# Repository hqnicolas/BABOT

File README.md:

# BaBot: Advanced 3-DOF Stewart- Gough Ball-Balancing Robot

An autonomous high-precision ball-balancing instrument predicated on a 3-DOF Stewart-Gough parallel kinematic mechanism. Powered by an ESP32-S3 microcontroller, the system integrates custom KiCad PCB hardware, a high-density 16-channel IR sensory array, and an asynchronous WebSocket-driven control interface for real-time telemetry and PID optimization.

This project represents a modern realization of parallel robotics, bridging classical control theory with contemporary high-frequency embedded systems.

https://github.com/user-attachments/assets/6e9986bd-6b06-4d86-9c46-4f5fcbdaf4ec

**License:** [Creative Commons Attribution-NonCommercial 4.0 International](LICENSE)

---

## Quick Start

### Prerequisites

- Arduino IDE with ESP32 board support
- ESP32-S3 development board or compatible target
- Physical BaBot hardware assembled

### Compilation

1. Open `firmware/firmware.ino` in Arduino IDE.
2. Select **ESP32S3 Dev Module** or your specific ESP32-S3 variant.
3. Click **Compile**.

On Windows, the helper script is also available:

```powershell
.\scripts\compile.ps1
```

### First Boot

1. Power on the robot.
2. Wait for the ESP32-S3 Wi-Fi access point.
3. Connect to Wi-Fi network `12345678` using password `12345678`.
4. Open `http://192.168.4.1/`.
5. The live control dashboard loads with telemetry and runtime controls.

---

## Features

- **Precision 3-DOF Stewart Platform** - A high-rigidity parallel kinematic architecture utilizing three independent actuator branches for precise control of posture and stability.
- **Async Web Control Ecosystem** - Low-latency dual-core dashboard featuring real-time state visualization, ball trajectory overlays, and holistic system diagnostics via WebSockets.
- **High-Density IR Sensory Matrix** - 16-channel infrared detection grid employing signed signal processing and individual multiplexer channel compensation.
- **Synchronized 30Hz Control Loop** - Deterministic real-time control orchestrated by a dedicated FreeRTOS sensor task, ensuring minimal phase lag between optical acquisition and mechanical actuation.
- **Machine Learning PID Autotune** - Autonomous gain discovery utilizing a Multi-Stage CMA-ES (Covariance Matrix Adaptation Evolution Strategy) search algorithm for noise-tolerant feedback optimization.
- **Mathematical Kinematics Solver** - Native C++ real-time implementation of Stewart-Gough inverse kinematics, eliminating the need for legacy lookup tables or offline pre-computation.
- **Robust Fail-Safe Architecture** - Multi-stage subsystem health monitoring with automated recovery protocols and persistent NVS calibration storage.

---

## Firmware Modules

| Module | Purpose |
|---|---|
| `firmware.ino` | Arduino `setup()`/`loop()` orchestration, hardware object composition, and shared runtime state |
| `ButtonInput.h` | Boot-button press decoding and lightweight status LED stubs |
| `ControlLoop.h` | PID, capture impulse, motion grace, telemetry publication, and closed-loop reset helpers |
| `PidAutotune.h` | Safe relay PID autotune state machine, metrics, gain estimation, start/cancel/restore |
| `StartupManager.h` | Bench-safe startup, subsystem health, degraded-mode policy, and deferred hardware bring-up |
| `ModeHandlers.h` | ON/OFF/test/calibration/assembly/position-test mode behavior |
| `UiCommandHandler.h` | Web UI command dispatch, runtime patching, persistence commands, and MUX compensation |
| `BoardConfig.h` | Pin definitions, mux layout, timing, PID defaults, and firmware constants |
| `RuntimeState` | Shared telemetry/config state, UI command queue, status models, and NVS runtime persistence |
| `PlatformControl` | Stewart-platform inverse kinematics and servo commands |
| `IRSensorArray` | Single-mux IR reading, signed signal processing, MUX compensation, ball detection, and centroid calculation |
| `X9C104Digipot` | Digital potentiometer control for IR LED brightness tuning |
| `WebUiServer` | HTTP server, WebSocket telemetry, embedded Web UI, and UI command parsing |
| `DebugLogger` | Async serial logging queue flushed from the Wi-Fi task |

---

## Hardware Pinout

ESP32-S3 control pins are defined in `firmware/src/BoardConfig.h`.

| Signal | GPIO | Notes |
|---|---:|---|
| `SERVO_A` | 41 | Servo output A |
| `SERVO_B` | 2 | Servo output B |
| `SERVO_C` | 1 | Servo output C |
| `IR_LED_CONTROL` | 45 | IR illumination control |
| `BOOT_BUTTON` | 0 | Runtime app button, active-low |
| `U12_CS` | 14 | X9C104 chip select |
| `U12_INCREMENT` | 12 | X9C104 increment |
| `U12_UP/DOWN` | 13 | X9C104 direction |
| `U1_S0` | 40 | CD74HC4067 select line |
| `U1_S1` | 39 | CD74HC4067 select line |
| `U1_S2` | 48 | CD74HC4067 select line |
| `U1_S3` | 47 | CD74HC4067 select line |
| `U1_SIG` | 9 | Multiplexed ADC input |

GPIO 19 and 20 are reserved for ESP32-S3 USB D-/D+.

---

## Operation Modes

### OFF

Platform leveled, no active balancing.

### ON

- No ball detected: platform idles level.
- Fast ball entry or edge approach: capture impulse tilts toward center with normal ON-mode authority up to `20 deg`.
- Ball detected and slowed: velocity-scaled PID keeps the ball centered.
- Recent ball loss: firmware briefly holds the last tilt command, then levels and resets closed-loop state.

### ASSEMBLY

Manual one-servo-at-a-time diagnostic mode for validating mechanical assembly and range of motion.

### CALIBRATION

Interactive servo offset calibration. Offsets are persisted to NVS when calibration completes.

### TEST / INDIVIDUAL_TEST / POSITION_TEST

Open-loop platform diagnostics and synthetic ball-position tests for bring-up. `POSITION_TEST` injects a circular synthetic ball position and runs the normal ON controller, so it exercises the current runtime PID, capture behavior, setpoint, and tilt limits.

---

## Web Dashboard

Once connected to the Wi-Fi AP:

1. **Control Panel** - Tilt visualization, ball position overlay, and mode selector.
2. **Telemetry** - Real-time sensor readings, servo positions, PID state, and system status.
3. **PID Autotune** - Safe relay feedback with measured noise floor, Ku/Pu estimation, capture + PD validation, and small I-value tests.
4. **Configuration and runtime** - Digipot tap, ball threshold, setpoint, PID gains, Save Runtime, Load Runtime, and Reset Defaults.
5. **Tests and calibration** - Servo tests, position tests, assembly/calibration modes, and individual MUX compensation.

All changes sync bidirectionally over WebSocket.

---

## PID Autotune

The **PID Autotune** drawer uses safe relay feedback while actively trying to keep the ball on the tray.

1. It waits for a ball entry inside the safe operating radius.
2. It briefly levels the platform and measures optical/electrical jitter as a noise floor.
3. It runs relay feedback on X and Y with hysteresis greater than the measured noise.
4. It aborts an individual relay attempt if radius, velocity, or detection loss indicate risk, then recovers and waits for a new safe entry.
5. It estimates conservative `Ku`/`Pu`, calculates PD gains, and tests capture + PD.
6. It evaluates only tiny I values: `0.000`, `0.005`, `0.010`, and `0.020`.

Autotune relay tilt is limited to `15 deg`. ON mode can still use the normal `20 deg` platform authority. If relay response remains too noisy or unsafe after repeated safety aborts, autotune fails safely, levels the platform, and restores the previous runtime PID/capture settings. Successful autotune applies values in RAM only; **Save Runtime** remains the only NVS persistence step.

---

## Key Runtime Constants

| Constant | Current value | Notes |
|---|---:|---|
| `kControlIntervalUs` | `33333` | 30 Hz Nominal control periodicity |
| `kProportionalGain` | `3.4` | Optimized legacy proportional gain |
| `kIntegralGain` | `0.06` | Optimized legacy integral gain |
| `kDerivativeGain` | `12.0` | Optimized legacy derivative gain |
| `kPlateHeightMm` | `115.0` | Design vertical height (Nominal) |
| `kMaxPlateTiltDeg` | `15.0` | Symmetrical mechanical safety authority |
| `kBallThreshold` | `30.0` | Signed IR detection floor |

---

## Bring-Up Checklist

- [ ] Compile firmware without errors.
- [ ] Flash to ESP32-S3 via USB.
- [ ] Connect to the `12345678` Wi-Fi AP and open `http://192.168.4.1/`.
- [ ] Confirm subsystems report ready or clear degraded-state messages.
- [ ] Test `ASSEMBLY` and `CALIBRATION` modes before balancing.
- [ ] Run individual MUX compensation after sensor or lighting changes.
- [ ] Tune digipot tap and ball threshold on real hardware.
- [ ] Test ON mode with slow and moderate ball entries.
- [ ] Run PID Autotune with safe ball entries and verify noise floor, relay crossings, Ku/Pu, confidence, and estimated P/D before saving runtime values.

---

## Third-Party Libraries

Vendored libraries live in `firmware/src/third_party/`:

- ArduinoJson - JSON serialization for web communication under `firmware/src/third_party/ArduinoJson/src`
- Servo - ESP32 servo PWM output
- WebSockets - Bidirectional WebSocket communication
- CD74HC4067 - 16-channel multiplexer control

For versions, upstream sources, and licenses, see [docs/third-party-sources.md](docs/third-party-sources.md).

---

## Documentation

| Document | Content |
|---|---|
| Document | Content |
|---|---|
| [docs/kinematics-theory.md](docs/kinematics-theory.md) | **Maturity Thesis**: Stewart-Gough derivation and system geometry |
| [docs/code-reference.md](docs/code-reference.md) | Firmware architecture, CMA-ES Autotune model, and module responsibilities |
| [docs/hardware-guide.md](docs/hardware-guide.md) | Mechanical assembly and PCB asset organization |
| [docs/autotune-tutorial.md](docs/autotune-tutorial.md) | Procedural guide for autonomous PID optimization |

---

## Safety Notes

- The robot starts in `OFF` mode on power-up.
- Always test on a stable, non-slip surface.
- Keep hands clear of linkages while servos are active.
- Do not use PID Autotune on a partially assembled or mechanically loose platform.
- If autotune reports relay response too noisy or unsafe, improve sensing/mechanics before applying gains.

---

## Contact & Support

https://www.ba-bot.com
https://www.ba-bot.com/manual/

#  License
This project is licensed under the Creative Commons Attribution-NonCommercial 4.0 International License.

#  Contact
For inquiries or support, please contact: info@ba-bot.com

---
# BABOT

The open-source ball-balancing robot you build, program, and bring to life.

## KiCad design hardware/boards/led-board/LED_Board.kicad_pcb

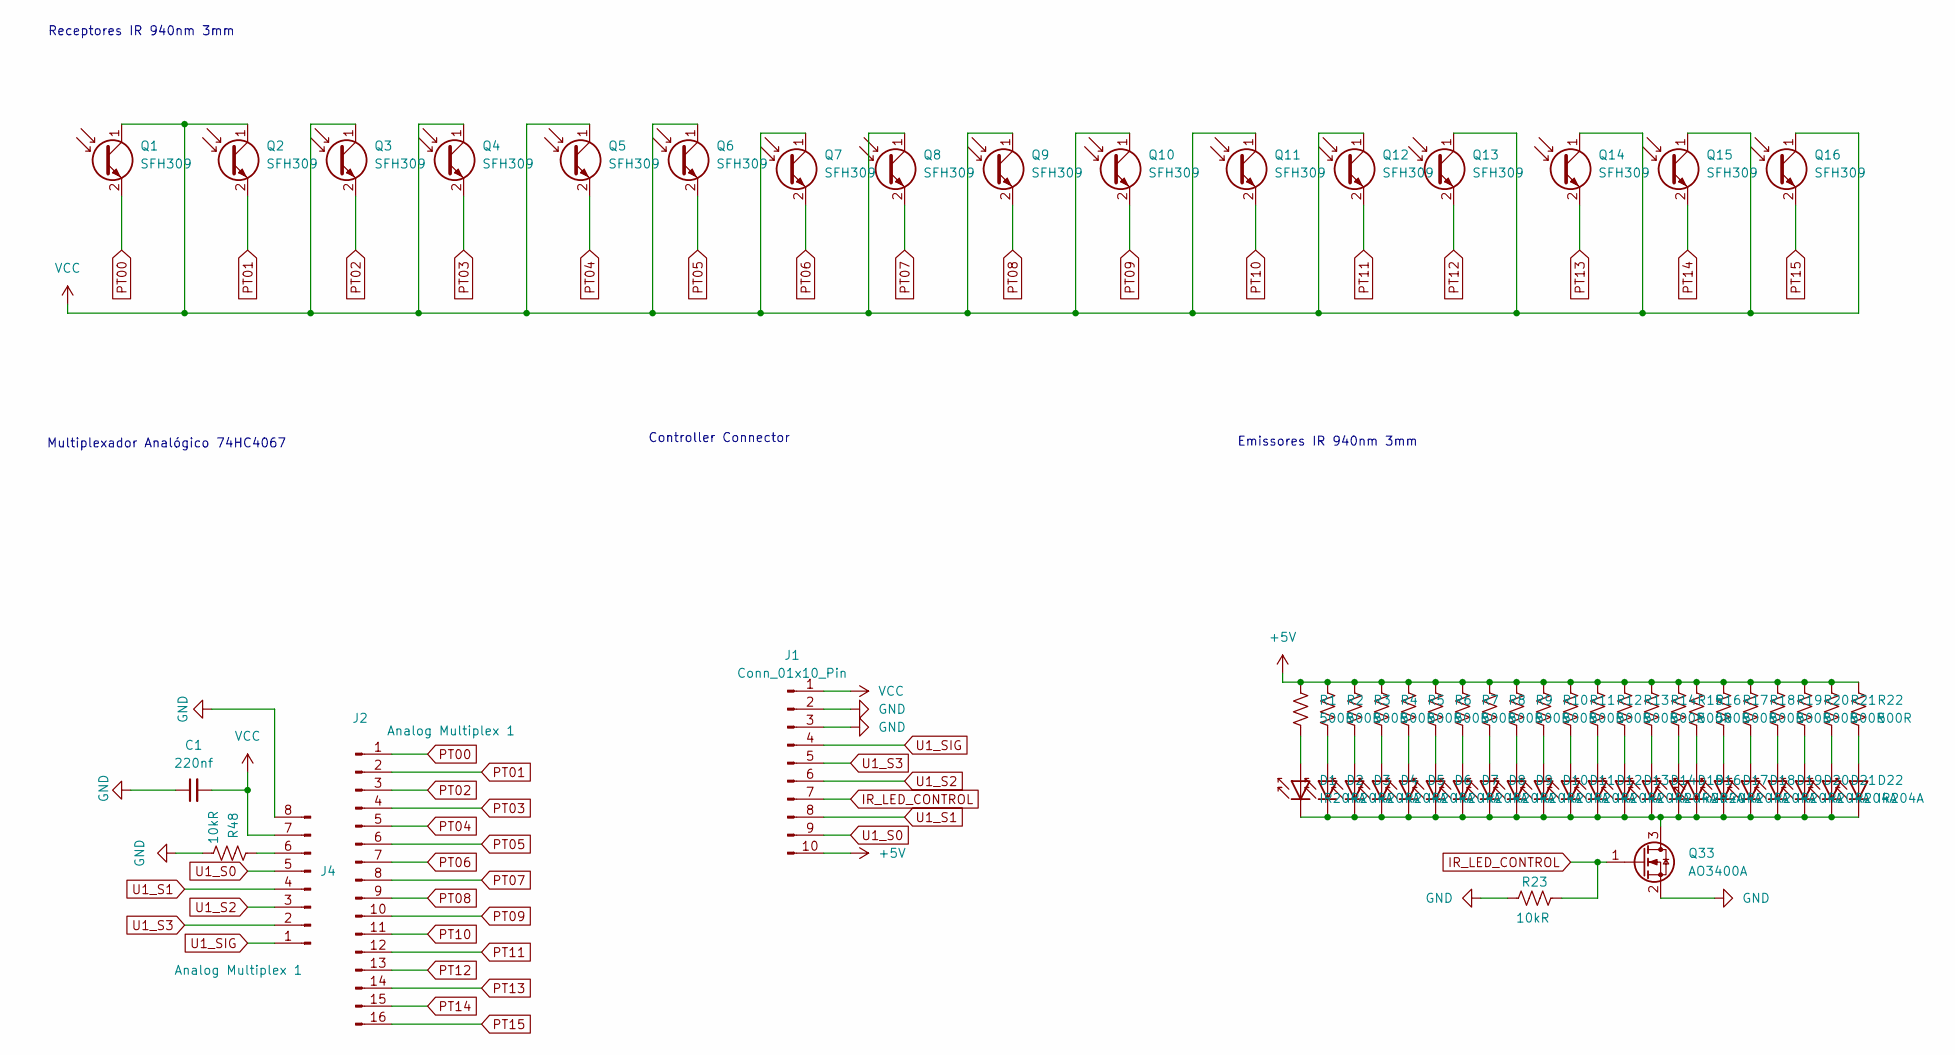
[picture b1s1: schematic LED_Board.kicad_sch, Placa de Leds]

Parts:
C1: 220nf; C_Disc_D7.5mm_W5.0mm_P10.00mm
D1, D2, D3, D4, D5, D6, D7, D8, D9, D10, D11, D12, D13, D14, D15, D16, D17, D18, D19, D20, D21, D22: IR204A; LED_D3.0mm_IRBlack
J1: Conn_01x10_Pin; PinSocket_1x10_P2.54mm_Vertical
J2: Analog Multiplex 1; PinHeader_1x16_P2.54mm_Vertical
J4: Analog Multiplex 1; PinHeader_1x08_P2.54mm_Vertical
Q1, Q2, Q3, Q4, Q5, Q6, Q7, Q8, Q9, Q10, Q11, Q12, Q13, Q14, Q15, Q16: SFH309; LED_D3.0mm_Clear
Q33: AO3400A; SOT-23
R1, R2, R3, R4, R5, R6, R7, R8, R9, R10, R11, R12, R13, R14, R15, R16, R17, R18, R19, R20, R21, R22: 500R; R_Axial_DIN0204_L3.6mm_D1.6mm_P5.08mm_Horizontal
R23, R48: 10kR; R_Axial_DIN0204_L3.6mm_D1.6mm_P5.08mm_Horizontal

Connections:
+5V: J1.10, R1.1, R2.1, R3.1, R4.1, R5.1, R6.1, R7.1, R8.1, R9.1, R10.1, R11.1, R12.1, R13.1, R14.1, R15.1, R16.1, R17.1, R18.1, R19.1, R20.1, R21.1, R22.1
GND: C1.1, J1.2, J1.3, J4.8, Q33.2 (S), R23.1, R48.2
IR_LED_CONTROL: J1.7, Q33.1 (G), R23.2
unnamed: D1.2 (A), R1.2
unnamed: D1.1 (K), D2.1 (K), D3.1 (K), D4.1 (K), D5.1 (K), D6.1 (K), D7.1 (K), D8.1 (K), D9.1 (K), D10.1 (K), D11.1 (K), D12.1 (K), D13.1 (K), D14.1 (K), D15.1 (K), D16.1 (K), D17.1 (K), D18.1 (K), D19.1 (K), D20.1 (K), D21.1 (K), D22.1 (K), Q33.3 (D)
unnamed: D2.2 (A), R2.2
unnamed: D3.2 (A), R3.2
unnamed: D4.2 (A), R4.2
unnamed: D5.2 (A), R5.2
unnamed: D6.2 (A), R6.2
unnamed: D7.2 (A), R7.2
unnamed: D8.2 (A), R8.2
unnamed: D9.2 (A), R9.2
unnamed: D10.2 (A), R10.2
unnamed: D11.2 (A), R11.2
unnamed: D12.2 (A), R12.2
unnamed: D13.2 (A), R13.2
unnamed: D14.2 (A), R14.2
unnamed: D15.2 (A), R15.2
unnamed: D16.2 (A), R16.2
unnamed: D17.2 (A), R17.2
unnamed: D18.2 (A), R18.2
unnamed: D19.2 (A), R19.2
unnamed: D20.2 (A), R20.2
unnamed: D21.2 (A), R21.2
unnamed: D22.2 (A), R22.2
unnamed: J4.6, R48.1
PT00: J2.1, Q1.2 (E)
PT01: J2.2, Q2.2 (E)
PT02: J2.3, Q3.2 (E)
PT03: J2.4, Q4.2 (E)
PT04: J2.5, Q5.2 (E)
PT05: J2.6, Q6.2 (E)
PT06: J2.7, Q7.2 (E)
PT07: J2.8, Q8.2 (E)
PT08: J2.9, Q9.2 (E)
PT09: J2.10, Q10.2 (E)
PT10: J2.11, Q11.2 (E)
PT11: J2.12, Q12.2 (E)
PT12: J2.13, Q13.2 (E)
PT13: J2.14, Q14.2 (E)
PT14: J2.15, Q15.2 (E)
PT15: J2.16, Q16.2 (E)
U1_S0: J1.9, J4.5
U1_S1: J1.8, J4.4
U1_S2: J1.6, J4.3
U1_S3: J1.5, J4.2
U1_SIG: J1.4, J4.1
VCC: C1.2, J1.1, J4.7, Q1.1 (C), Q2.1 (C), Q3.1 (C), Q4.1 (C), Q5.1 (C), Q6.1 (C), Q7.1 (C), Q8.1 (C), Q9.1 (C), Q10.1 (C), Q11.1 (C), Q12.1 (C), Q13.1 (C), Q14.1 (C), Q15.1 (C), Q16.1 (C)

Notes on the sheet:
Receptores IR 940nm 3mm
Controller Connector
Emissores IR 940nm 3mm
Multiplexador Analógico 74HC4067

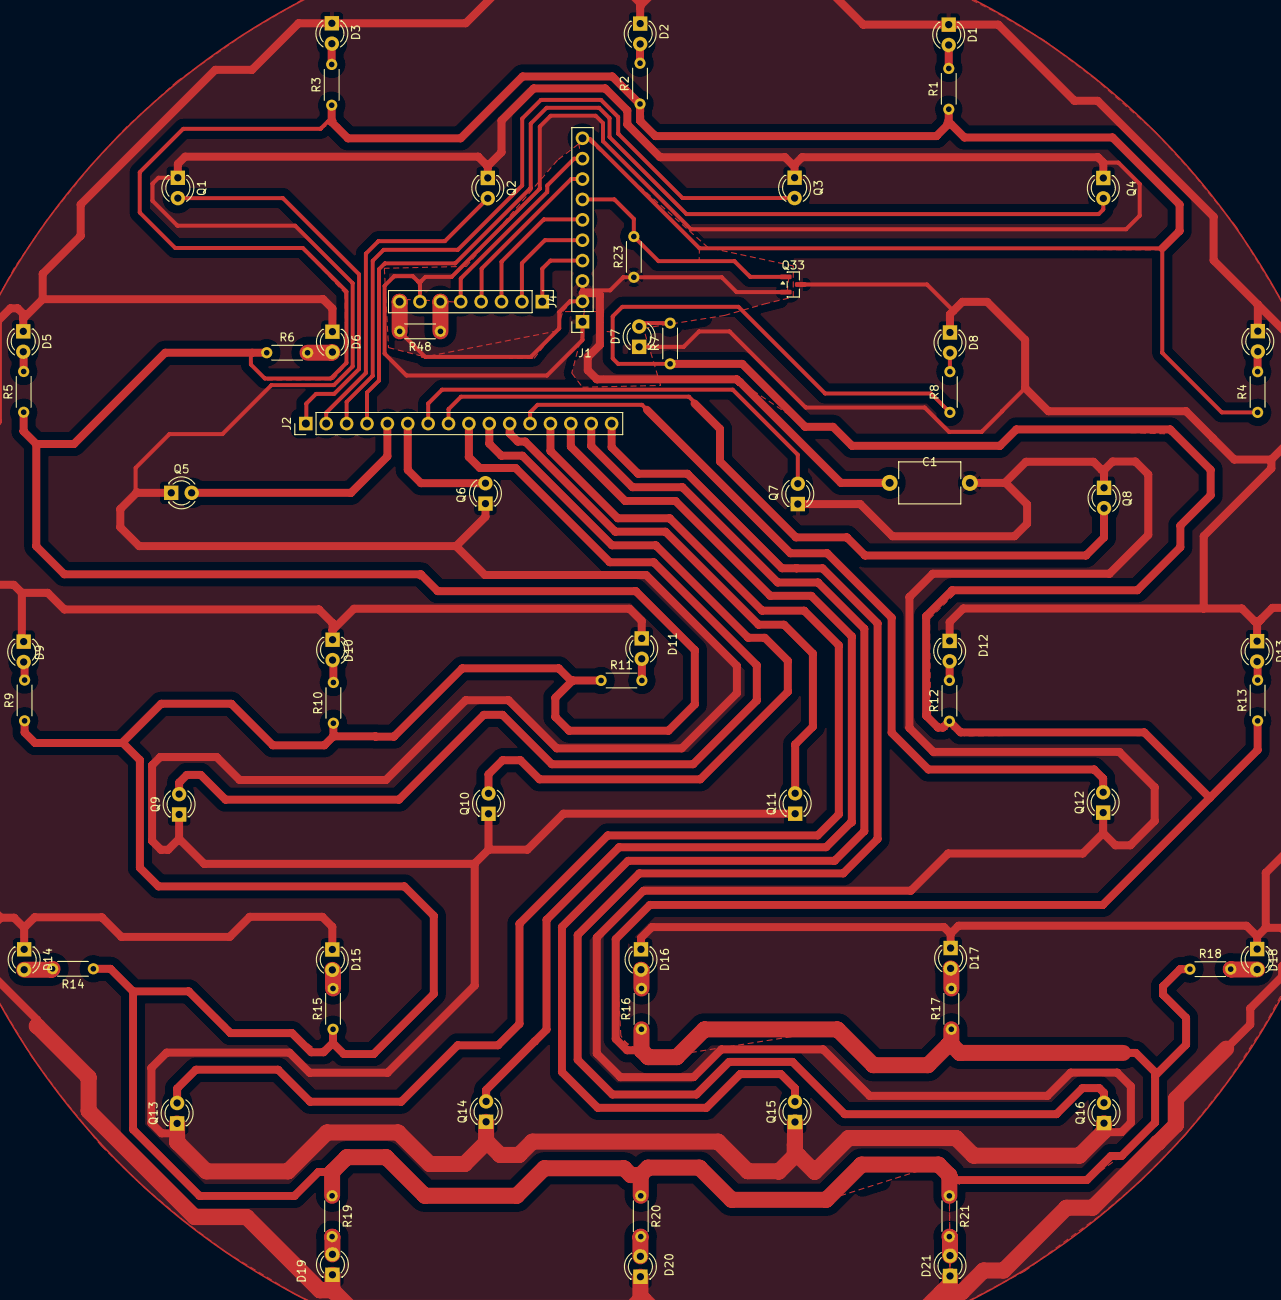
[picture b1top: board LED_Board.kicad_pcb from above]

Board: 2 copper layers, 65 parts (0 on the bottom side), 48 nets.

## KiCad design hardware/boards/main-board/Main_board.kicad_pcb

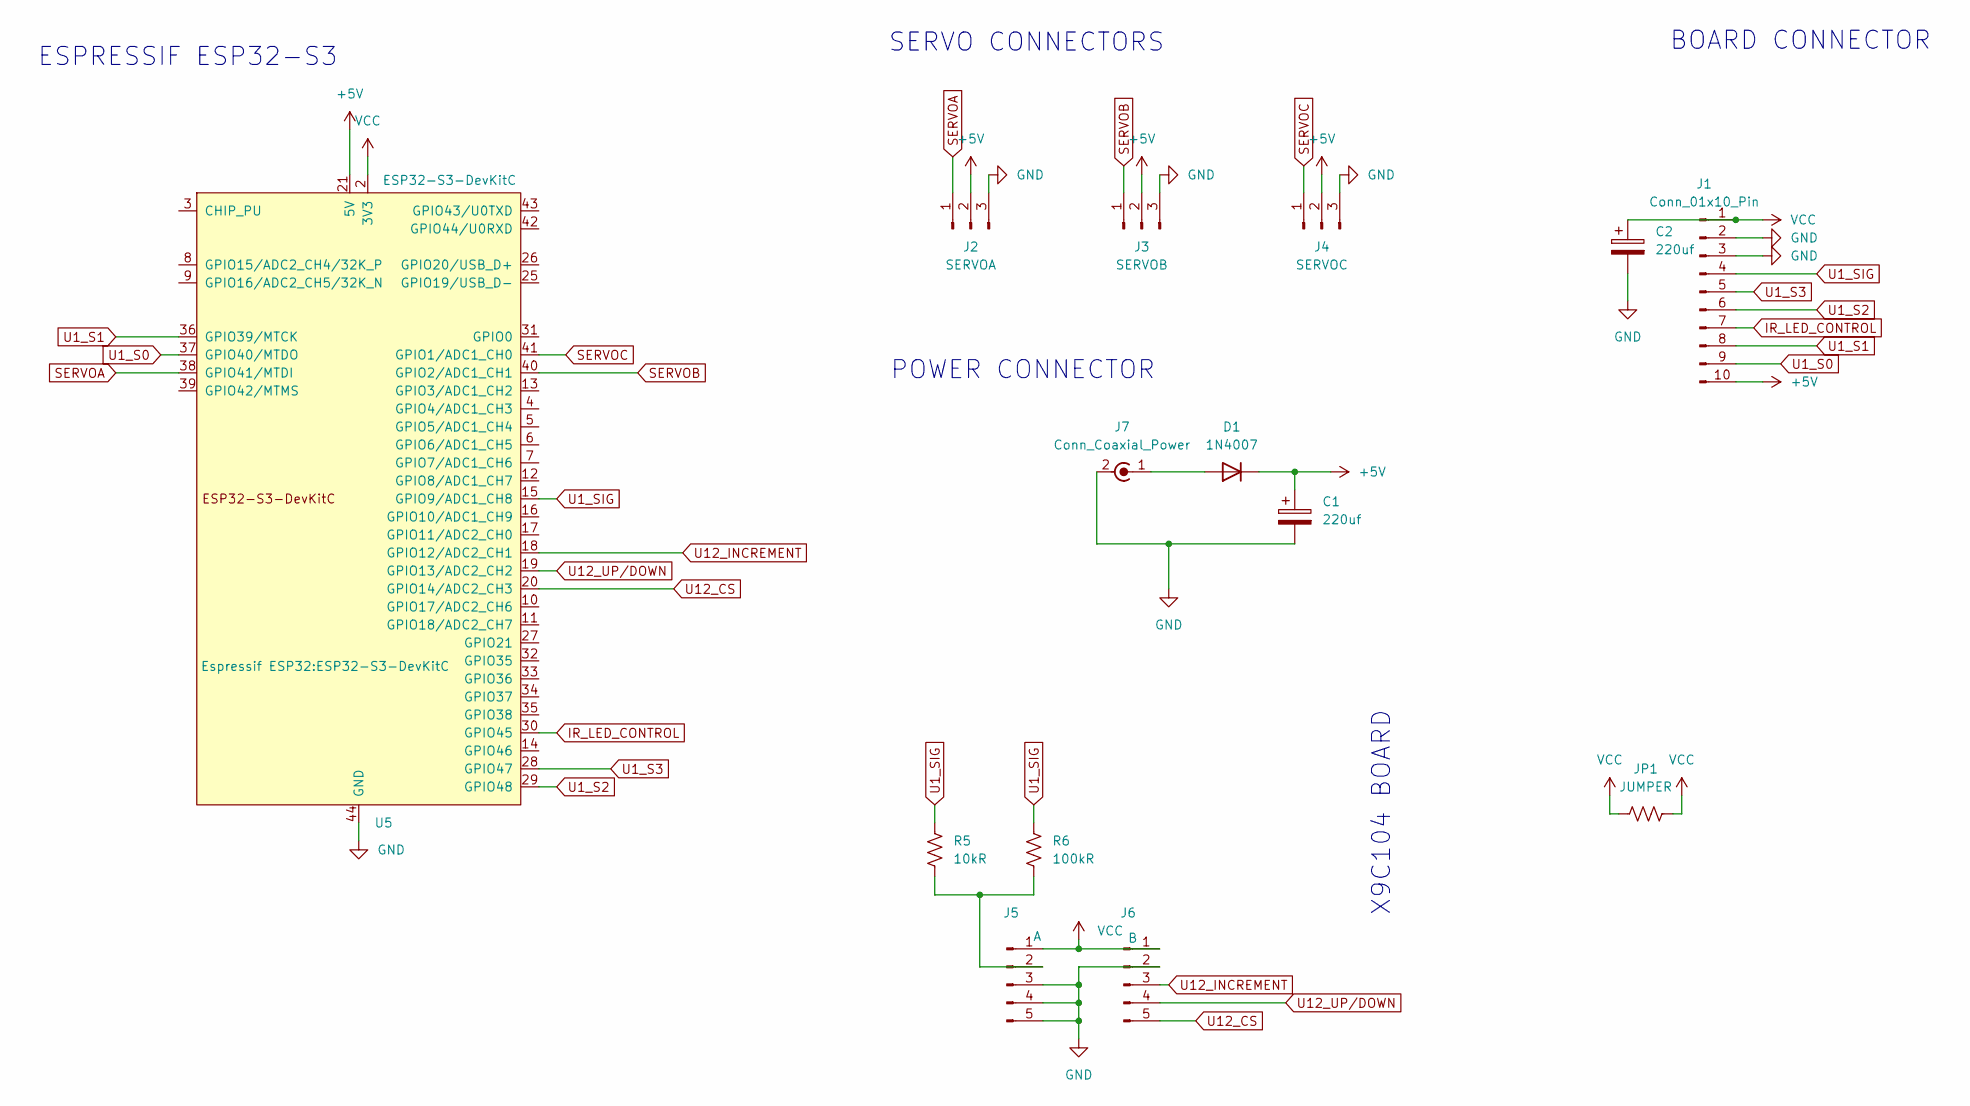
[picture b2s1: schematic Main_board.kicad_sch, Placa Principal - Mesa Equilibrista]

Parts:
C1, C2: 220uf; CP_Radial_D10.0mm_P5.00mm
D1: 1N4007; D_DO-41_SOD81_P10.16mm_Horizontal
J1: Conn_01x10_Pin; PinHeader_1x10_P2.54mm_Vertical
J2: SERVOA; PinHeader_1x03_P2.54mm_Vertical
J3: SERVOB; PinHeader_1x03_P2.54mm_Vertical
J4: SERVOC; PinHeader_1x03_P2.54mm_Vertical
J5: A; PinHeader_1x05_P2.54mm_Vertical
J6: B; PinHeader_1x05_P2.54mm_Vertical
J7: Conn_Coaxial_Power; L_Axial_L9.5mm_D4.0mm_P5.08mm_Vertical_Fastron_SMCC
JP1: JUMPER; R_Axial_DIN0204_L3.6mm_D1.6mm_P5.08mm_Horizontal
R5: 10kR; R_Axial_DIN0204_L3.6mm_D1.6mm_P5.08mm_Horizontal
R6: 100kR; R_Axial_DIN0204_L3.6mm_D1.6mm_P5.08mm_Horizontal
U5: ESP32-S3-DevKitC

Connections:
+5V: C1.1, D1.1 (K), J1.10, J2.2, J3.2, J4.2, U5.21 (5V)
GND: C1.2, C2.2, J1.2, J1.3, J2.3, J3.3, J4.3, J5.3, J5.4, J5.5, J6.2, J7.2 (Ext), U5.22 (GND), U5.23 (GND), U5.24 (GND), U5.44 (GND)
IR_LED_CONTROL: J1.7, U5.30 (GPIO45)
unnamed: D1.2 (A), J7.1 (In)
unnamed: J5.2, R5.2, R6.2
SERVOA: J2.1, U5.38 (GPIO41/MTDI)
SERVOB: J3.1, U5.40 (GPIO2/ADC1_CH1)
SERVOC: J4.1, U5.41 (GPIO1/ADC1_CH0)
U1_S0: J1.9, U5.37 (GPIO40/MTDO)
U1_S1: J1.8, U5.36 (GPIO39/MTCK)
U1_S2: J1.6, U5.29 (GPIO48)
U1_S3: J1.5, U5.28 (GPIO47)
U1_SIG: J1.4, R5.1, R6.1, U5.15 (GPIO9/ADC1_CH8)
U12_CS: J6.5, U5.20 (GPIO14/ADC2_CH3)
U12_INCREMENT: J6.3, U5.18 (GPIO12/ADC2_CH1)
U12_UP/DOWN: J6.4, U5.19 (GPIO13/ADC2_CH2)
VCC: C2.1, J1.1, J5.1, J6.1, JP1.1, JP1.2, U5.1 (3V3), U5.2 (3V3)

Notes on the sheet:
X9C104 BOARD
ESPRESSIF ESP32-S3
SERVO CONNECTORS
BOARD CONNECTOR
POWER CONNECTOR

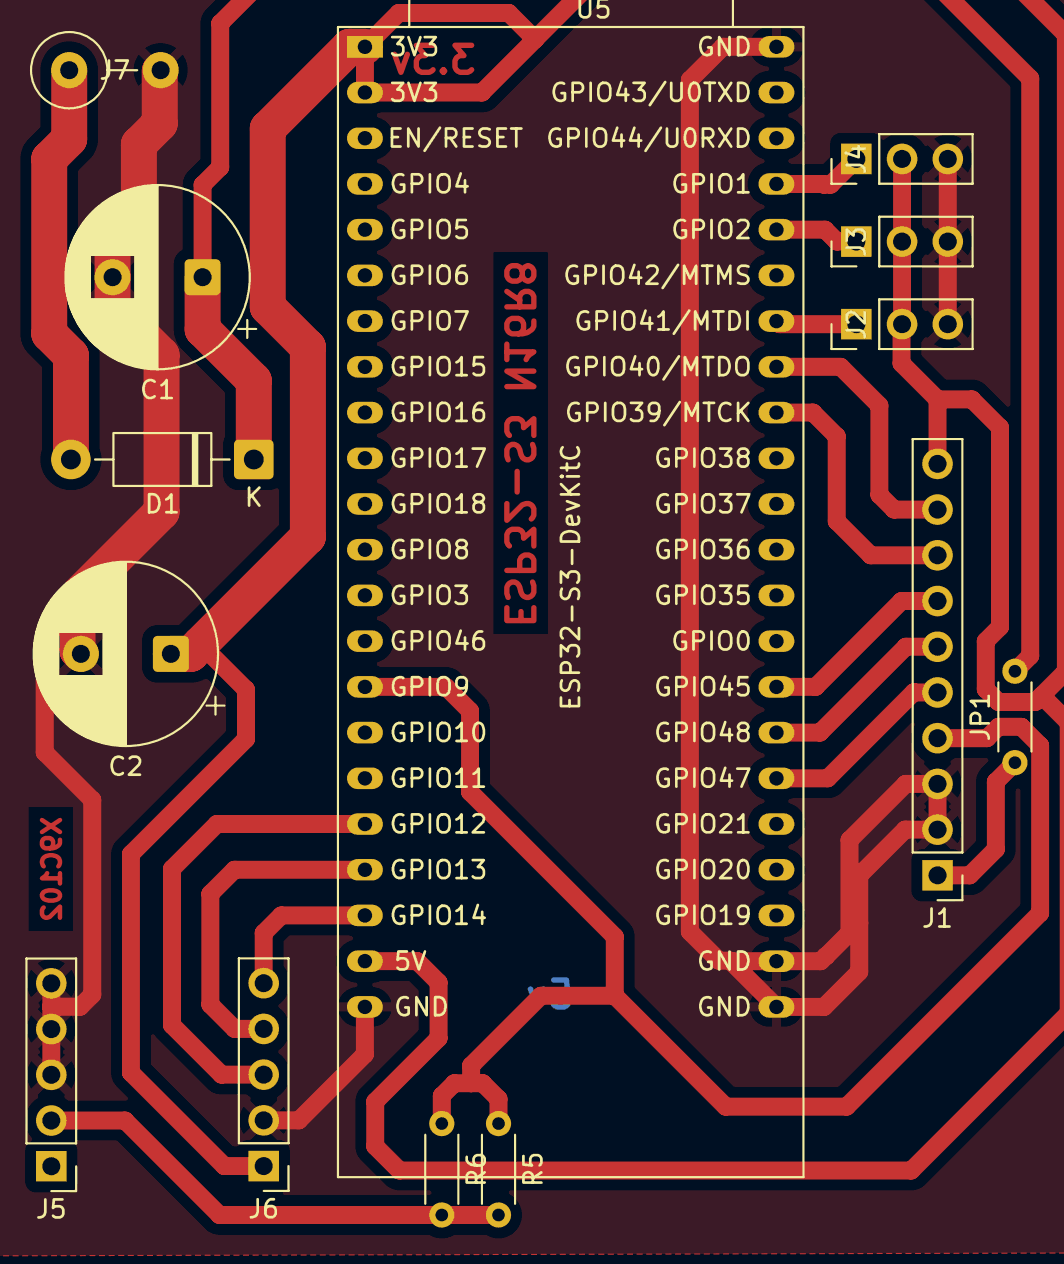
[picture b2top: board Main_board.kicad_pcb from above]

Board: 2 copper layers, 14 parts (0 on the bottom side), 17 nets.

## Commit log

2026-04-27 Release
2026-04-27 Remove Auto Catcher
2026-04-27 Remove Catcher Telemetry
2026-04-27 Readme
